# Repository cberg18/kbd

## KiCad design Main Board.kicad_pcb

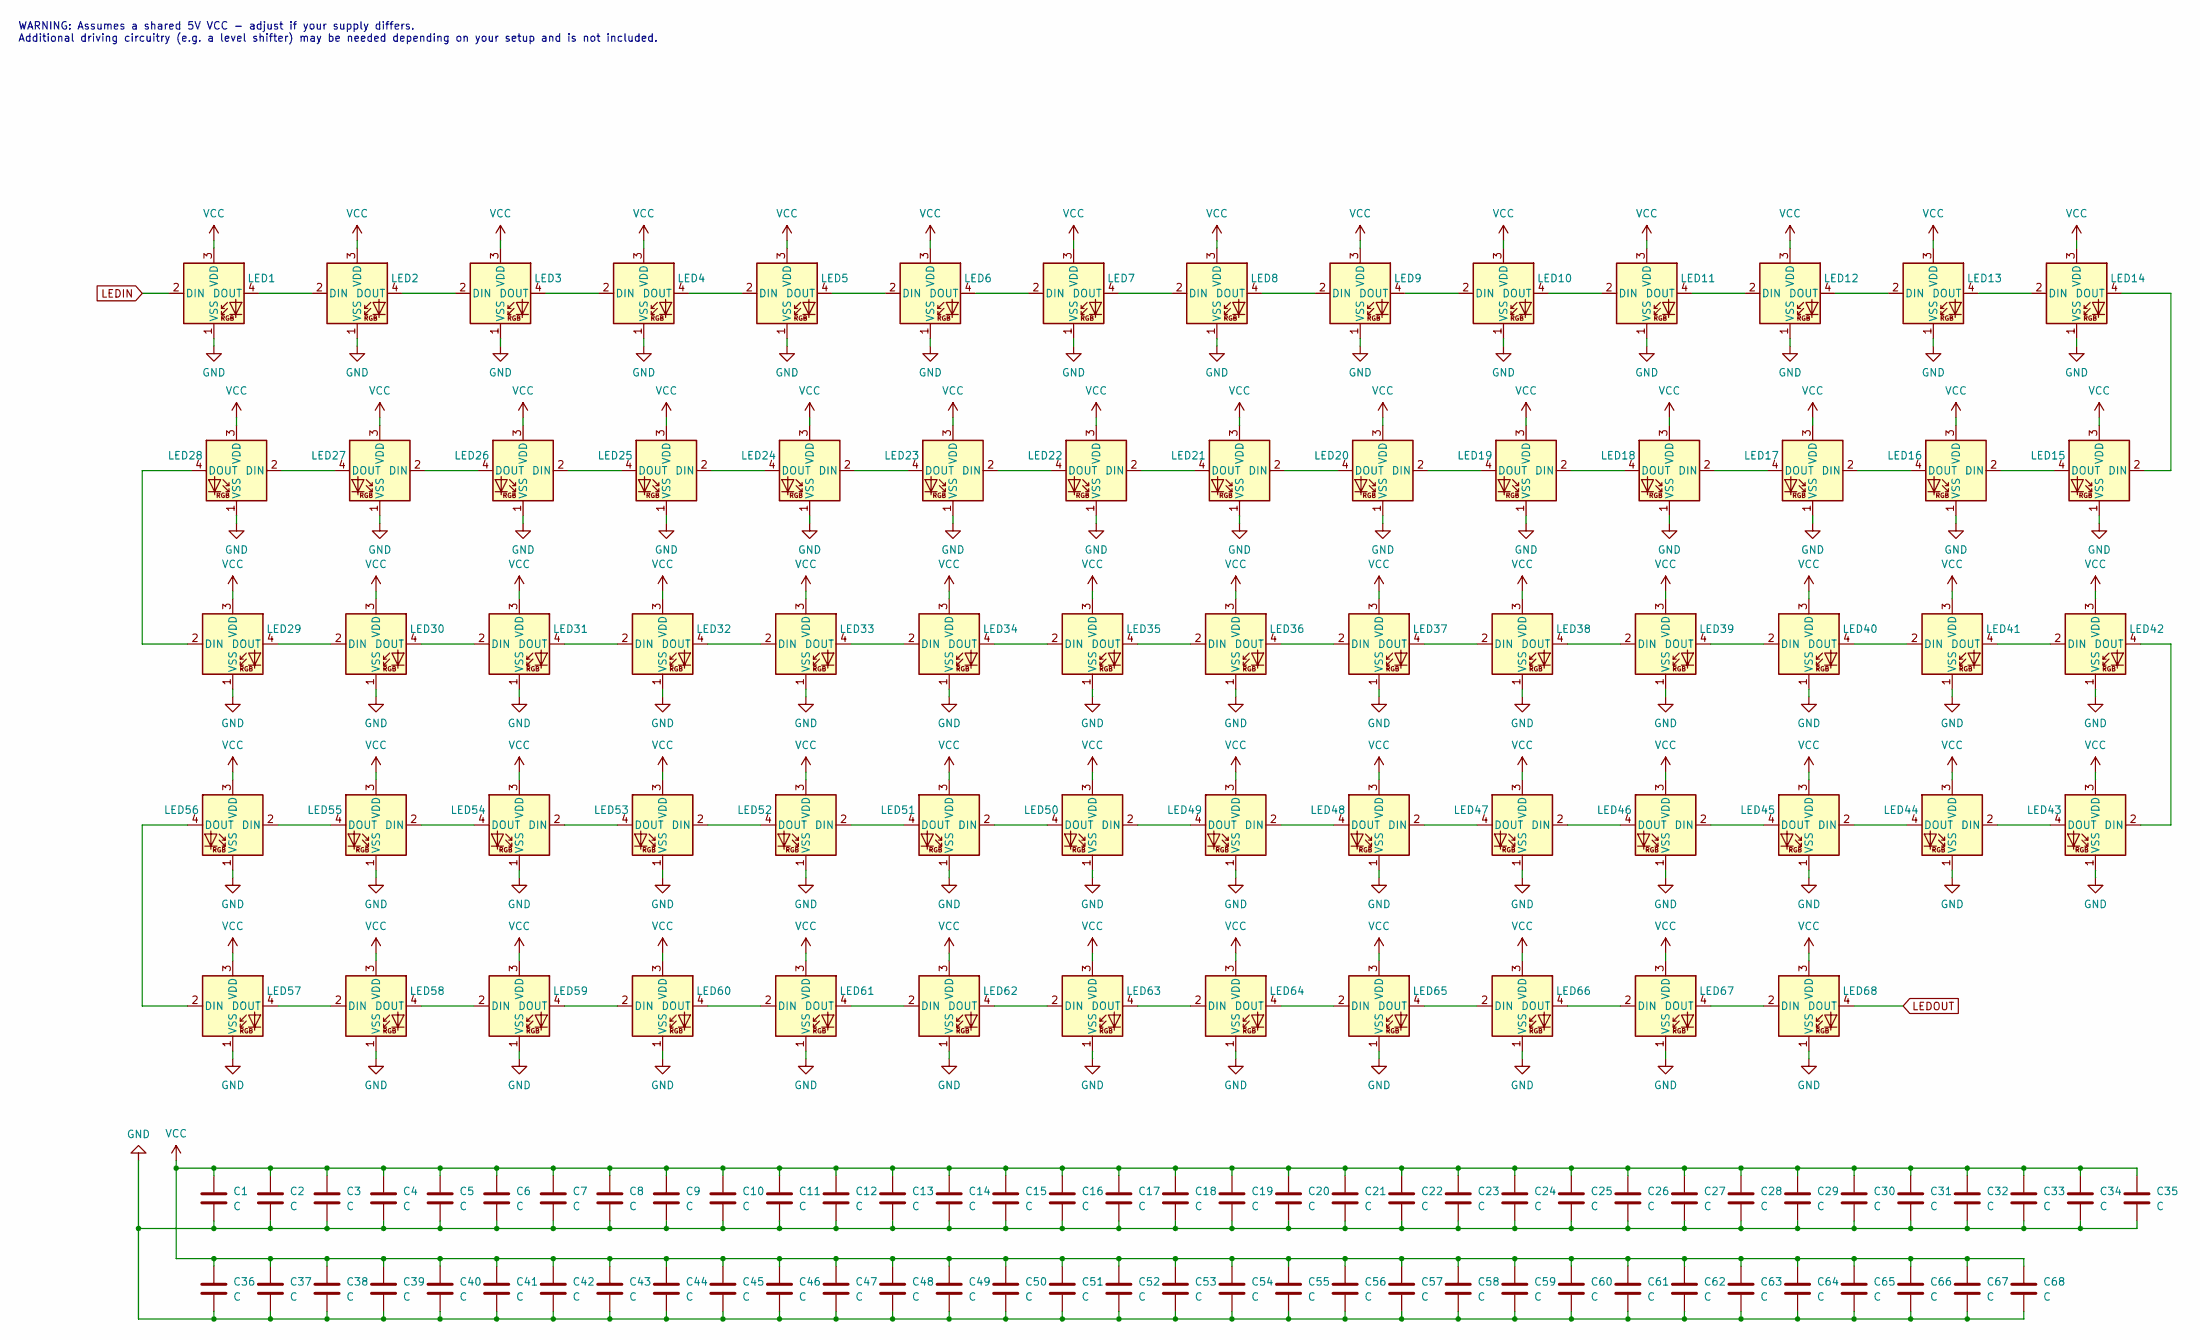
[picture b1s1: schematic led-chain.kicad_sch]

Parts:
C1, C2, C3, C4, C5, C6, C7, C8, C9, C10, C11, C12, C13, C14, C15, C16, C17, C18, C19, C20, C21, C22, C23, C24, C25, C26, C27, C28, C29, C30, C31, C32, C33, C34, C35, C36, C37, C38, C39, C40, C41, C42, C43, C44, C45, C46, C47, C48, C49, C50, C51, C52, C53, C54, C55, C56, C57, C58, C59, C60, C61, C62, C63, C64, C65, C66, C67, C68: C; C_0603_1608Metric
LED1, LED2, LED3, LED4, LED5, LED6, LED7, LED8, LED9, LED10, LED11, LED12, LED13, LED14, LED15, LED16, LED17, LED18, LED19, LED20, LED21, LED22, LED23, LED24, LED25, LED26, LED27, LED28, LED29, LED30, LED31, LED32, LED33, LED34, LED35, LED36, LED37, LED38, LED39, LED40, LED41, LED42, LED43, LED44, LED45, LED46, LED47, LED48, LED49, LED50, LED51, LED52, LED53, LED54, LED55, LED56, LED57, LED58, LED59, LED60, LED61, LED62, LED63, LED64, LED65, LED66, LED67, LED68: SK6812MINI-E; LED_SK6812MINI-E_3.2x2.8mm_P1.5mm_ReverseMount

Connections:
GND: C1.2, C2.2, C3.2, C4.2, C5.2, C6.2, C7.2, C8.2, C9.2, C10.2, C11.2, C12.2, C13.2, C14.2, C15.2, C16.2, C17.2, C18.2, C19.2, C20.2, C21.2, C22.2, C23.2, C24.2, C25.2, C26.2, C27.2, C28.2, C29.2, C30.2, C31.2, C32.2, C33.2, C34.2, C35.2, C36.2, C37.2, C38.2, C39.2, C40.2, C41.2, C42.2, C43.2, C44.2, C45.2, C46.2, C47.2, C48.2, C49.2, C50.2, C51.2, C52.2, C53.2, C54.2, C55.2, C56.2, C57.2, C58.2, C59.2, C60.2, C61.2, C62.2, C63.2, C64.2, C65.2, C66.2, C67.2, C68.2, LED1.1 (VSS), LED2.1 (VSS), LED3.1 (VSS), LED4.1 (VSS), LED5.1 (VSS), LED6.1 (VSS), LED7.1 (VSS), LED8.1 (VSS), LED9.1 (VSS), LED10.1 (VSS), LED11.1 (VSS), LED12.1 (VSS), LED13.1 (VSS), LED14.1 (VSS), LED15.1 (VSS), LED16.1 (VSS), LED17.1 (VSS), LED18.1 (VSS), LED19.1 (VSS), LED20.1 (VSS), LED21.1 (VSS), LED22.1 (VSS), LED23.1 (VSS), LED24.1 (VSS), LED25.1 (VSS), LED26.1 (VSS), LED27.1 (VSS), LED28.1 (VSS), LED29.1 (VSS), LED30.1 (VSS), LED31.1 (VSS), LED32.1 (VSS), LED33.1 (VSS), LED34.1 (VSS), LED35.1 (VSS), LED36.1 (VSS), LED37.1 (VSS), LED38.1 (VSS), LED39.1 (VSS), LED40.1 (VSS), LED41.1 (VSS), LED42.1 (VSS), LED43.1 (VSS), LED44.1 (VSS), LED45.1 (VSS), LED46.1 (VSS), LED47.1 (VSS), LED48.1 (VSS), LED49.1 (VSS), LED50.1 (VSS), LED51.1 (VSS), LED52.1 (VSS), LED53.1 (VSS), LED54.1 (VSS), LED55.1 (VSS), LED56.1 (VSS), LED57.1 (VSS), LED58.1 (VSS), LED59.1 (VSS), LED60.1 (VSS), LED61.1 (VSS), LED62.1 (VSS), LED63.1 (VSS), LED64.1 (VSS), LED65.1 (VSS), LED66.1 (VSS), LED67.1 (VSS), LED68.1 (VSS); also elsewhere on the board
LEDOUT: LED68.4 (DOUT)
unnamed: LED1.4 (DOUT), LED2.2 (DIN)
unnamed: LED2.4 (DOUT), LED3.2 (DIN)
unnamed: LED3.4 (DOUT), LED4.2 (DIN)
unnamed: LED4.4 (DOUT), LED5.2 (DIN)
unnamed: LED5.4 (DOUT), LED6.2 (DIN)
unnamed: LED6.4 (DOUT), LED7.2 (DIN)
unnamed: LED7.4 (DOUT), LED8.2 (DIN)
unnamed: LED8.4 (DOUT), LED9.2 (DIN)
unnamed: LED9.4 (DOUT), LED10.2 (DIN)
unnamed: LED10.4 (DOUT), LED11.2 (DIN)
unnamed: LED11.4 (DOUT), LED12.2 (DIN)
unnamed: LED12.4 (DOUT), LED13.2 (DIN)
unnamed: LED13.4 (DOUT), LED14.2 (DIN)
unnamed: LED14.4 (DOUT), LED15.2 (DIN)
unnamed: LED15.4 (DOUT), LED16.2 (DIN)
unnamed: LED16.4 (DOUT), LED17.2 (DIN)
unnamed: LED17.4 (DOUT), LED18.2 (DIN)
unnamed: LED18.4 (DOUT), LED19.2 (DIN)
unnamed: LED19.4 (DOUT), LED20.2 (DIN)
unnamed: LED20.4 (DOUT), LED21.2 (DIN)
unnamed: LED21.4 (DOUT), LED22.2 (DIN)
unnamed: LED22.4 (DOUT), LED23.2 (DIN)
unnamed: LED23.4 (DOUT), LED24.2 (DIN)
unnamed: LED24.4 (DOUT), LED25.2 (DIN)
unnamed: LED25.4 (DOUT), LED26.2 (DIN)
unnamed: LED26.4 (DOUT), LED27.2 (DIN)
unnamed: LED27.4 (DOUT), LED28.2 (DIN)
unnamed: LED28.4 (DOUT), LED29.2 (DIN)
unnamed: LED29.4 (DOUT), LED30.2 (DIN)
unnamed: LED30.4 (DOUT), LED31.2 (DIN)
unnamed: LED31.4 (DOUT), LED32.2 (DIN)
unnamed: LED32.4 (DOUT), LED33.2 (DIN)
unnamed: LED33.4 (DOUT), LED34.2 (DIN)
unnamed: LED34.4 (DOUT), LED35.2 (DIN)
unnamed: LED35.4 (DOUT), LED36.2 (DIN)
unnamed: LED36.4 (DOUT), LED37.2 (DIN)
unnamed: LED37.4 (DOUT), LED38.2 (DIN)
unnamed: LED38.4 (DOUT), LED39.2 (DIN)
unnamed: LED39.4 (DOUT), LED40.2 (DIN)
unnamed: LED40.4 (DOUT), LED41.2 (DIN)
unnamed: LED41.4 (DOUT), LED42.2 (DIN)
unnamed: LED42.4 (DOUT), LED43.2 (DIN)
unnamed: LED43.4 (DOUT), LED44.2 (DIN)
unnamed: LED44.4 (DOUT), LED45.2 (DIN)
unnamed: LED45.4 (DOUT), LED46.2 (DIN)
unnamed: LED46.4 (DOUT), LED47.2 (DIN)
unnamed: LED47.4 (DOUT), LED48.2 (DIN)
unnamed: LED48.4 (DOUT), LED49.2 (DIN)
unnamed: LED49.4 (DOUT), LED50.2 (DIN)
unnamed: LED50.4 (DOUT), LED51.2 (DIN)
unnamed: LED51.4 (DOUT), LED52.2 (DIN)
unnamed: LED52.4 (DOUT), LED53.2 (DIN)
unnamed: LED53.4 (DOUT), LED54.2 (DIN)
unnamed: LED54.4 (DOUT), LED55.2 (DIN)
unnamed: LED55.4 (DOUT), LED56.2 (DIN)
unnamed: LED56.4 (DOUT), LED57.2 (DIN)
unnamed: LED57.4 (DOUT), LED58.2 (DIN)
unnamed: LED58.4 (DOUT), LED59.2 (DIN)
unnamed: LED59.4 (DOUT), LED60.2 (DIN)
unnamed: LED60.4 (DOUT), LED61.2 (DIN)
unnamed: LED61.4 (DOUT), LED62.2 (DIN)
unnamed: LED62.4 (DOUT), LED63.2 (DIN)
unnamed: LED63.4 (DOUT), LED64.2 (DIN)
unnamed: LED64.4 (DOUT), LED65.2 (DIN)
unnamed: LED65.4 (DOUT), LED66.2 (DIN)
unnamed: LED66.4 (DOUT), LED67.2 (DIN)
unnamed: LED67.4 (DOUT), LED68.2 (DIN)
VCC: C1.1, C2.1, C3.1, C4.1, C5.1, C6.1, C7.1, C8.1, C9.1, C10.1, C11.1, C12.1, C13.1, C14.1, C15.1, C16.1, C17.1, C18.1, C19.1, C20.1, C21.1, C22.1, C23.1, C24.1, C25.1, C26.1, C27.1, C28.1, C29.1, C30.1, C31.1, C32.1, C33.1, C34.1, C35.1, C36.1, C37.1, C38.1, C39.1, C40.1, C41.1, C42.1, C43.1, C44.1, C45.1, C46.1, C47.1, C48.1, C49.1, C50.1, C51.1, C52.1, C53.1, C54.1, C55.1, C56.1, C57.1, C58.1, C59.1, C60.1, C61.1, C62.1, C63.1, C64.1, C65.1, C66.1, C67.1, C68.1, LED1.3 (VDD), LED2.3 (VDD), LED3.3 (VDD), LED4.3 (VDD), LED5.3 (VDD), LED6.3 (VDD), LED7.3 (VDD), LED8.3 (VDD), LED9.3 (VDD), LED10.3 (VDD), LED11.3 (VDD), LED12.3 (VDD), LED13.3 (VDD), LED14.3 (VDD), LED15.3 (VDD), LED16.3 (VDD), LED17.3 (VDD), LED18.3 (VDD), LED19.3 (VDD), LED20.3 (VDD), LED21.3 (VDD), LED22.3 (VDD), LED23.3 (VDD), LED24.3 (VDD), LED25.3 (VDD), LED26.3 (VDD), LED27.3 (VDD), LED28.3 (VDD), LED29.3 (VDD), LED30.3 (VDD), LED31.3 (VDD), LED32.3 (VDD), LED33.3 (VDD), LED34.3 (VDD), LED35.3 (VDD), LED36.3 (VDD), LED37.3 (VDD), LED38.3 (VDD), LED39.3 (VDD), LED40.3 (VDD), LED41.3 (VDD), LED42.3 (VDD), LED43.3 (VDD), LED44.3 (VDD), LED45.3 (VDD), LED46.3 (VDD), LED47.3 (VDD), LED48.3 (VDD), LED49.3 (VDD), LED50.3 (VDD), LED51.3 (VDD), LED52.3 (VDD), LED53.3 (VDD), LED54.3 (VDD), LED55.3 (VDD), LED56.3 (VDD), LED57.3 (VDD), LED58.3 (VDD), LED59.3 (VDD), LED60.3 (VDD), LED61.3 (VDD), LED62.3 (VDD), LED63.3 (VDD), LED64.3 (VDD), LED65.3 (VDD), LED66.3 (VDD), LED67.3 (VDD), LED68.3 (VDD); also elsewhere on the board

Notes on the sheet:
WARNING: Assumes a shared 5V VCC - adjust if your supply differs. Additional driving circuitry (e.g. a level shifter) may be needed depending on your setup and is not included.

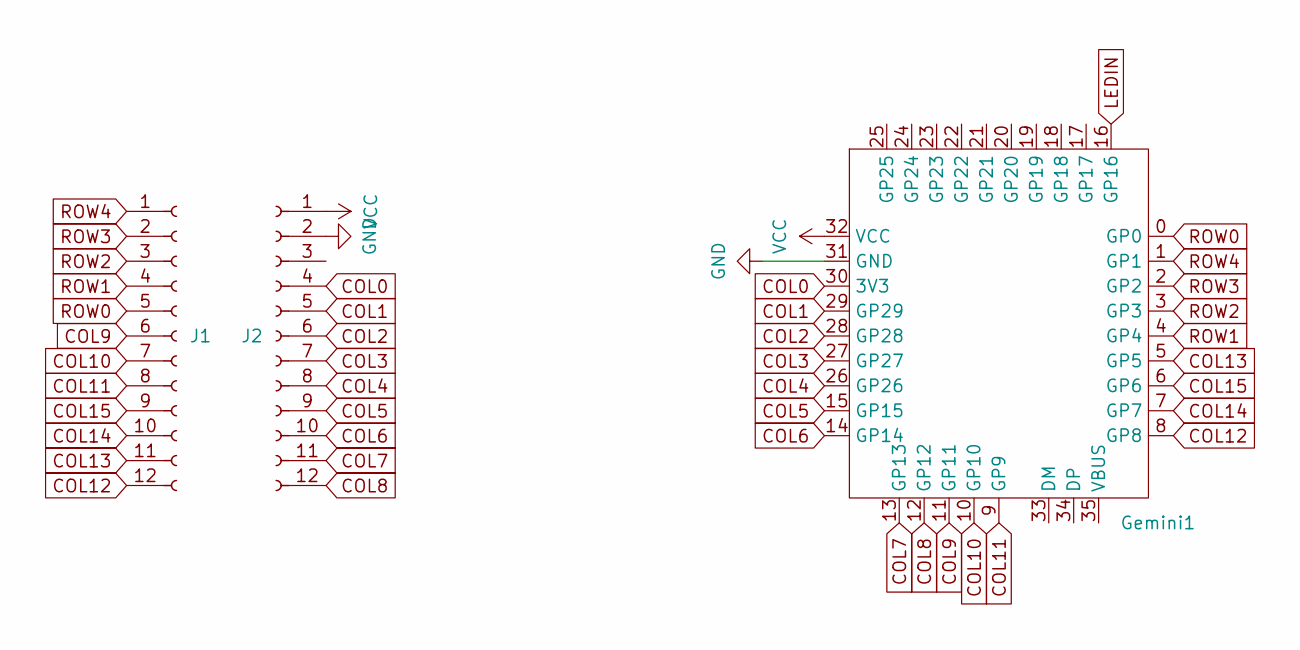
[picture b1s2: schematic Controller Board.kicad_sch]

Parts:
Gemini1: gemini
J1, J2: Conn_01x12_Socket; PinSocket_1x12_P2.54mm_Vertical

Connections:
COL1: Gemini1.29 (GP29), J2.5; also elsewhere on the board
COL2: Gemini1.28 (GP28), J2.6; also elsewhere on the board
COL3: Gemini1.27 (GP27), J2.7; also elsewhere on the board
COL4: Gemini1.26 (GP26), J2.8; also elsewhere on the board
COL5: Gemini1.15 (GP15), J2.9; also elsewhere on the board
COL6: Gemini1.14 (GP14), J2.10; also elsewhere on the board
COL7: Gemini1.13 (GP13), J2.11; also elsewhere on the board
COL8: Gemini1.12 (GP12), J2.12; also elsewhere on the board
COL9: Gemini1.11 (GP11), J1.6; also elsewhere on the board
COL10: Gemini1.10 (GP10), J1.7; also elsewhere on the board
COL11: Gemini1.9 (GP9), J1.8; also elsewhere on the board
COL13: Gemini1.5 (GP5), J1.11; also elsewhere on the board
COL14: Gemini1.7 (GP7), J1.10; also elsewhere on the board
GND: Gemini1.31 (GND), J2.2; also elsewhere on the board
ROW0: Gemini1.0 (GP0), J1.5; also elsewhere on the board
ROW1: Gemini1.4 (GP4), J1.4; also elsewhere on the board
ROW2: Gemini1.3 (GP3), J1.3; also elsewhere on the board
ROW4: Gemini1.1 (GP1), J1.1; also elsewhere on the board
VCC: Gemini1.32 (VCC), J2.1; also elsewhere on the board

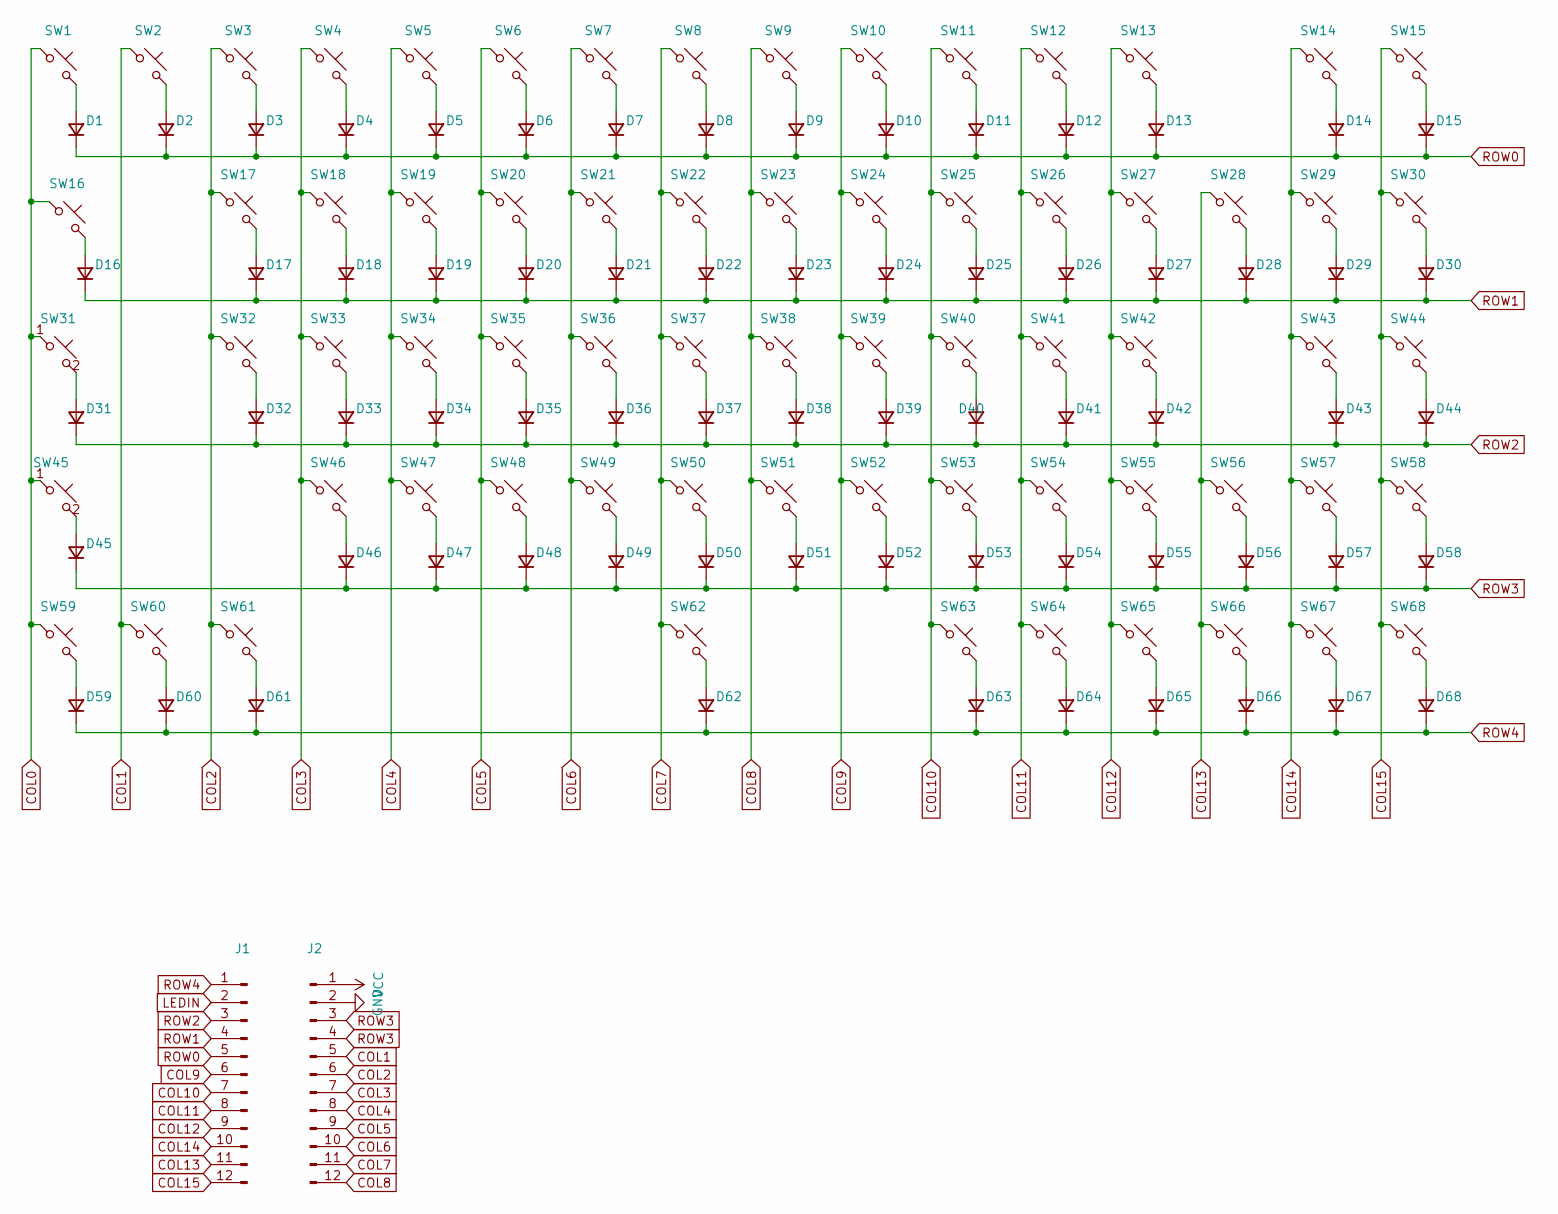
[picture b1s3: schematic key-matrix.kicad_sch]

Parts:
D1, D2, D3, D4, D5, D6, D7, D8, D9, D10, D11, D12, D13, D14, D15, D16, D17, D18, D19, D20, D21, D22, D23, D24, D25, D26, D27, D28, D29, D30, D31, D32, D33, D34, D35, D36, D37, D38, D39, D40, D41, D42, D43, D44, D45, D46, D47, D48, D49, D50, D51, D52, D53, D54, D55, D56, D57, D58, D59, D60, D61, D62, D63, D64, D65, D66, D67, D68: D; D_SOD-123
J1, J2: Conn_01x12_Pin; PinSocket_1x12_P2.54mm_Vertical
SW1, SW2, SW3, SW4, SW5, SW6, SW7, SW8, SW9, SW10, SW11, SW12, SW13, SW14, SW15, SW16, SW17, SW18, SW19, SW20, SW21, SW22, SW23, SW24, SW25, SW26, SW27, SW28, SW29, SW30, SW31, SW32, SW33, SW34, SW35, SW36, SW37, SW38, SW39, SW40, SW41, SW42, SW43, SW44, SW45, SW46, SW47, SW48, SW49, SW50, SW51, SW52, SW53, SW54, SW55, SW56, SW57, SW58, SW59, SW60, SW61, SW62, SW63, SW64, SW65, SW66, SW67, SW68: SW_Push; MX-Hotswap-1U

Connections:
COL0: SW1.1, SW16.1, SW31.1, SW45.1, SW59.1
COL1: J2.5, SW2.1, SW60.1; also elsewhere on the board
COL2: J2.6, SW3.1, SW17.1, SW32.1, SW61.1; also elsewhere on the board
COL3: J2.7, SW4.1, SW18.1, SW33.1, SW46.1; also elsewhere on the board
COL4: J2.8, SW5.1, SW19.1, SW34.1, SW47.1; also elsewhere on the board
COL5: J2.9, SW6.1, SW20.1, SW35.1, SW48.1; also elsewhere on the board
COL6: J2.10, SW7.1, SW21.1, SW36.1, SW49.1; also elsewhere on the board
COL7: J2.11, SW8.1, SW22.1, SW37.1, SW50.1, SW62.1; also elsewhere on the board
COL8: J2.12, SW9.1, SW23.1, SW38.1, SW51.1; also elsewhere on the board
COL9: J1.6, SW10.1, SW24.1, SW39.1, SW52.1; also elsewhere on the board
COL10: J1.7, SW11.1, SW25.1, SW40.1, SW53.1, SW63.1; also elsewhere on the board
COL11: J1.8, SW12.1, SW26.1, SW41.1, SW54.1, SW64.1; also elsewhere on the board
COL13: J1.11, SW28.1, SW56.1, SW66.1; also elsewhere on the board
COL14: J1.10, SW14.1, SW29.1, SW43.1, SW57.1, SW67.1; also elsewhere on the board
GND: J2.2; also elsewhere on the board
unnamed: D1.2 (A), SW1.2
unnamed: D2.2 (A), SW2.2
unnamed: D3.2 (A), SW3.2
unnamed: D4.2 (A), SW4.2
unnamed: D5.2 (A), SW5.2
unnamed: D6.2 (A), SW6.2
unnamed: D7.2 (A), SW7.2
unnamed: D8.2 (A), SW8.2
unnamed: D9.2 (A), SW9.2
unnamed: D10.2 (A), SW10.2
unnamed: D11.2 (A), SW11.2
unnamed: D12.2 (A), SW12.2
unnamed: D13.2 (A), SW13.2
unnamed: D14.2 (A), SW14.2
unnamed: D15.2 (A), SW15.2
unnamed: D16.2 (A), SW16.2
unnamed: D17.2 (A), SW17.2
unnamed: D18.2 (A), SW18.2
unnamed: D19.2 (A), SW19.2
unnamed: D20.2 (A), SW20.2
unnamed: D21.2 (A), SW21.2
unnamed: D22.2 (A), SW22.2
unnamed: D23.2 (A), SW23.2
unnamed: D24.2 (A), SW24.2
unnamed: D25.2 (A), SW25.2
unnamed: D26.2 (A), SW26.2
unnamed: D27.2 (A), SW27.2
unnamed: D28.2 (A), SW28.2
unnamed: D29.2 (A), SW29.2
unnamed: D30.2 (A), SW30.2
unnamed: D31.2 (A), SW31.2
unnamed: D32.2 (A), SW32.2
unnamed: D33.2 (A), SW33.2
unnamed: D34.2 (A), SW34.2
unnamed: D35.2 (A), SW35.2
unnamed: D36.2 (A), SW36.2
unnamed: D37.2 (A), SW37.2
unnamed: D38.2 (A), SW38.2
unnamed: D39.2 (A), SW39.2
unnamed: D40.2 (A), SW40.2
unnamed: D41.2 (A), SW41.2
unnamed: D42.2 (A), SW42.2
unnamed: D43.2 (A), SW43.2
unnamed: D44.2 (A), SW44.2
unnamed: D45.2 (A), SW45.2
unnamed: D46.2 (A), SW46.2
unnamed: D47.2 (A), SW47.2
unnamed: D48.2 (A), SW48.2
unnamed: D49.2 (A), SW49.2
unnamed: D50.2 (A), SW50.2
unnamed: D51.2 (A), SW51.2
unnamed: D52.2 (A), SW52.2
unnamed: D53.2 (A), SW53.2
unnamed: D54.2 (A), SW54.2
unnamed: D55.2 (A), SW55.2
unnamed: D56.2 (A), SW56.2
unnamed: D57.2 (A), SW57.2
unnamed: D58.2 (A), SW58.2
unnamed: D59.2 (A), SW59.2
unnamed: D60.2 (A), SW60.2
unnamed: D61.2 (A), SW61.2
unnamed: D62.2 (A), SW62.2
unnamed: D63.2 (A), SW63.2
unnamed: D64.2 (A), SW64.2
unnamed: D65.2 (A), SW65.2
unnamed: D66.2 (A), SW66.2
unnamed: D67.2 (A), SW67.2
unnamed: D68.2 (A), SW68.2
ROW0: D1.1 (K), D2.1 (K), D3.1 (K), D4.1 (K), D5.1 (K), D6.1 (K), D7.1 (K), D8.1 (K), D9.1 (K), D10.1 (K), D11.1 (K), D12.1 (K), D13.1 (K), D14.1 (K), D15.1 (K), J1.5; also elsewhere on the board
ROW1: D16.1 (K), D17.1 (K), D18.1 (K), D19.1 (K), D20.1 (K), D21.1 (K), D22.1 (K), D23.1 (K), D24.1 (K), D25.1 (K), D26.1 (K), D27.1 (K), D28.1 (K), D29.1 (K), D30.1 (K), J1.4; also elsewhere on the board
ROW2: D31.1 (K), D32.1 (K), D33.1 (K), D34.1 (K), D35.1 (K), D36.1 (K), D37.1 (K), D38.1 (K), D39.1 (K), D40.1 (K), D41.1 (K), D42.1 (K), D43.1 (K), D44.1 (K), J1.3; also elsewhere on the board
ROW4: D59.1 (K), D60.1 (K), D61.1 (K), D62.1 (K), D63.1 (K), D64.1 (K), D65.1 (K), D66.1 (K), D67.1 (K), D68.1 (K), J1.1; also elsewhere on the board
VCC: J2.1; also elsewhere on the board

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
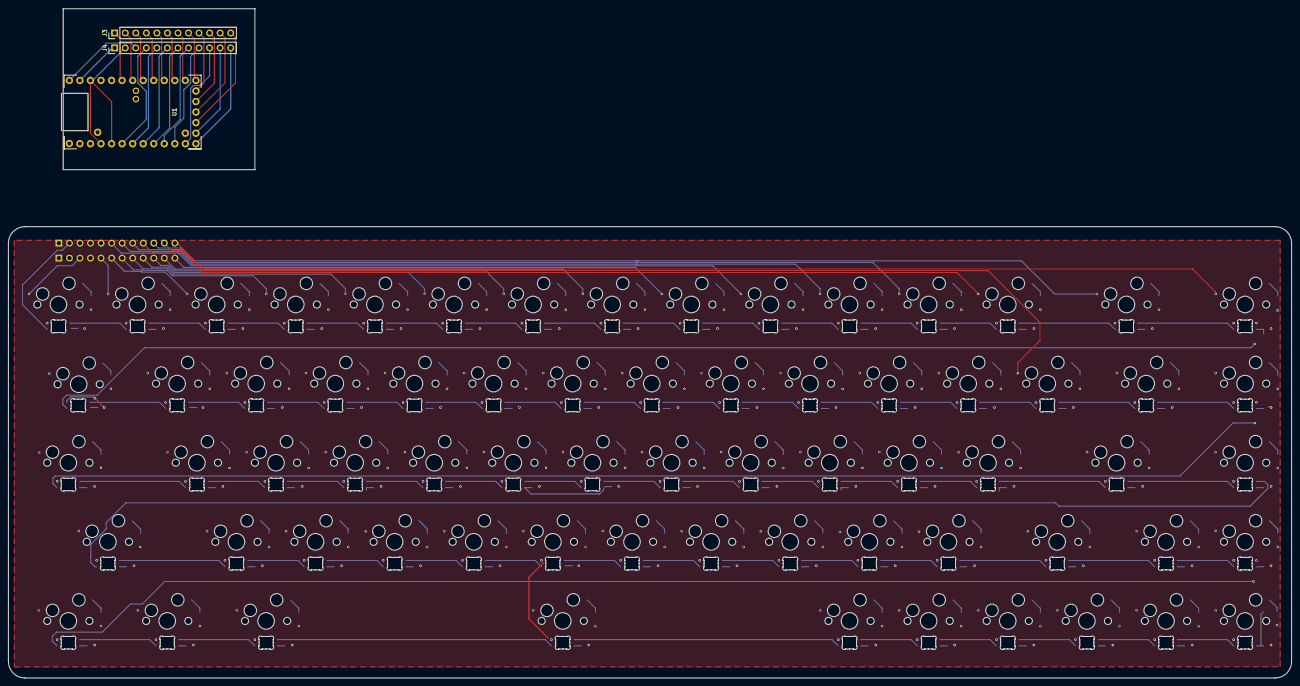
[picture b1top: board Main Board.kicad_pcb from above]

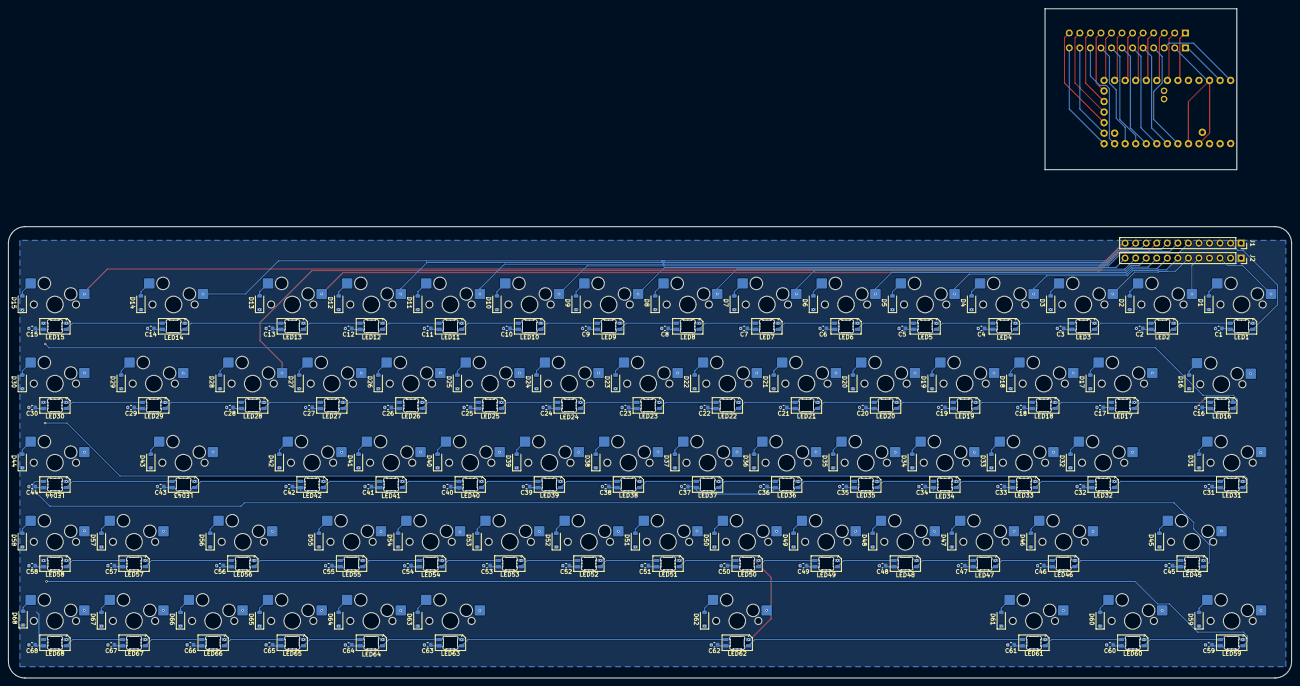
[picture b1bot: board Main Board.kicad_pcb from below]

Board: 4 copper layers, 309.0 x 108.7 mm, 277 parts (274 on the bottom side), 183 nets.

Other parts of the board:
J3, J4: Conn_01x12_Header; PinHeader_1x12_P2.54mm_Vertical
U1: pro_micro_rp2040

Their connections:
_COL0: J4.4, U1.2 (GP2)
_COL1: J4.5, U1.3 (GP3)
_COL2: J4.6, U1.4 (GP4)
_COL3: J4.7, U1.5 (GP5)
_COL4: J4.8, U1.6 (GP6)
_COL5: J4.9, U1.7 (GP7)
_COL6: J4.10, U1.8 (GP8)
_COL7: J4.11, U1.12 (GP12)
_COL8: J4.12, U1.9 (GP9)
_COL9: J3.6, U1.20 (GP20)
_COL10: J3.7, U1.23 (GP23)
_COL11: J3.8, U1.21 (GP21)
_COL12: J3.12, U1.13 (GP13)
_COL13: J3.11, U1.14 (GP14)
_COL14: J3.10, U1.15 (GP15)
_COL15: J3.9, U1.16 (GP16)
_GND: J4.2, U1.GND
_LEDIN: J4.3, U1.11 (GP11)
_ROW0: J3.5, U1.22 (GP22)
_ROW1: J3.4, U1.26 (GP26)
_ROW2: J3.3, U1.27 (GP27)
_ROW3: J3.2, U1.28 (GP28)
_ROW4: J3.1, U1.29 (GP29)
_VCC: J4.1, U1.5V

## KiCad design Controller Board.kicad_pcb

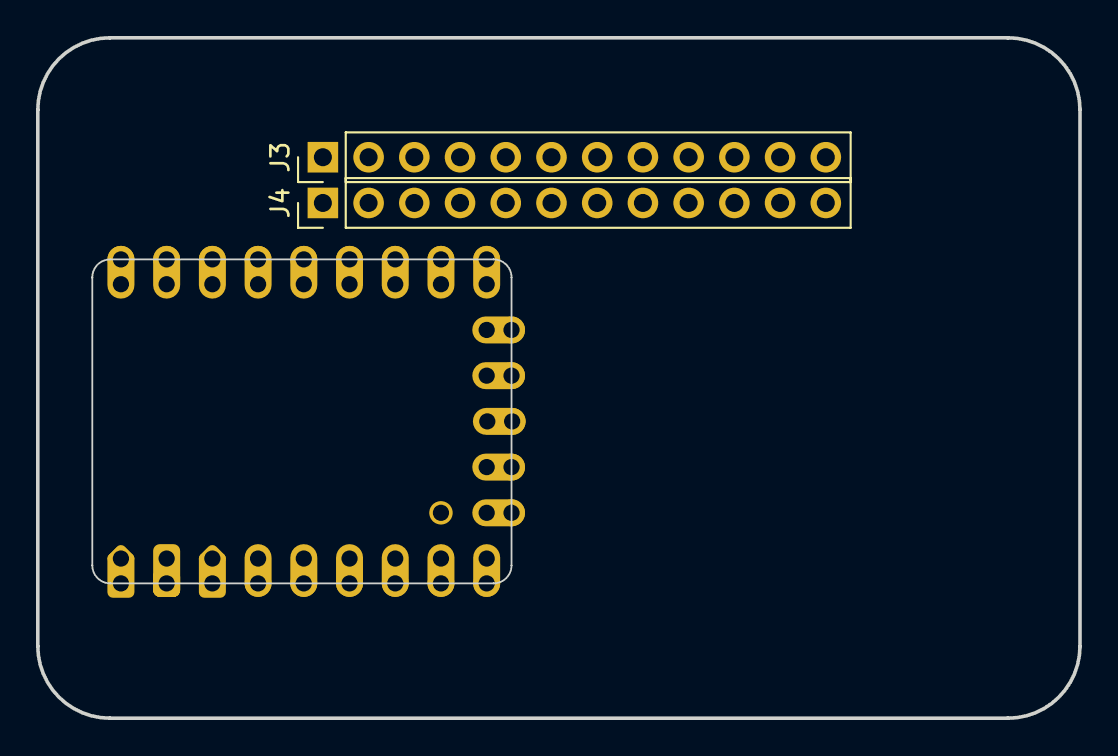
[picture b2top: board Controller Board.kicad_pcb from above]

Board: 4 copper layers, 57.9 x 37.8 mm, 3 parts (0 on the bottom side), 23 nets.

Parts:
Gemini1: gemini
J3, J4: Conn_01x12_Pin; PinHeader_1x12_P2.54mm_Vertical

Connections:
COL0: Gemini1.30 (3V3), J4.4
COL1: Gemini1.29 (GP29), J4.5
COL2: Gemini1.28 (GP28), J4.6
COL3: Gemini1.27 (GP27), J4.7
COL4: Gemini1.26 (GP26), J4.8
COL5: Gemini1.15 (GP15), J4.9
COL6: Gemini1.14 (GP14), J4.10
COL7: Gemini1.13 (GP13), J4.11
COL8: Gemini1.12 (GP12), J4.12
COL9: Gemini1.11 (GP11), J3.6
COL10: Gemini1.10 (GP10), J3.7
COL11: Gemini1.9 (GP9), J3.8
COL12: Gemini1.8 (GP8), J3.12
COL13: Gemini1.5 (GP5), J3.11
COL14: Gemini1.7 (GP7), J3.10
COL15: Gemini1.6 (GP6), J3.9
GND: Gemini1.31 (GND), J4.2
ROW0: Gemini1.0 (GP0), J3.5
ROW1: Gemini1.4 (GP4), J3.4
ROW2: Gemini1.3 (GP3), J3.3
ROW3: Gemini1.2 (GP2), J3.2
ROW4: Gemini1.1 (GP1), J3.1
VCC: Gemini1.32 (VCC), J4.1
